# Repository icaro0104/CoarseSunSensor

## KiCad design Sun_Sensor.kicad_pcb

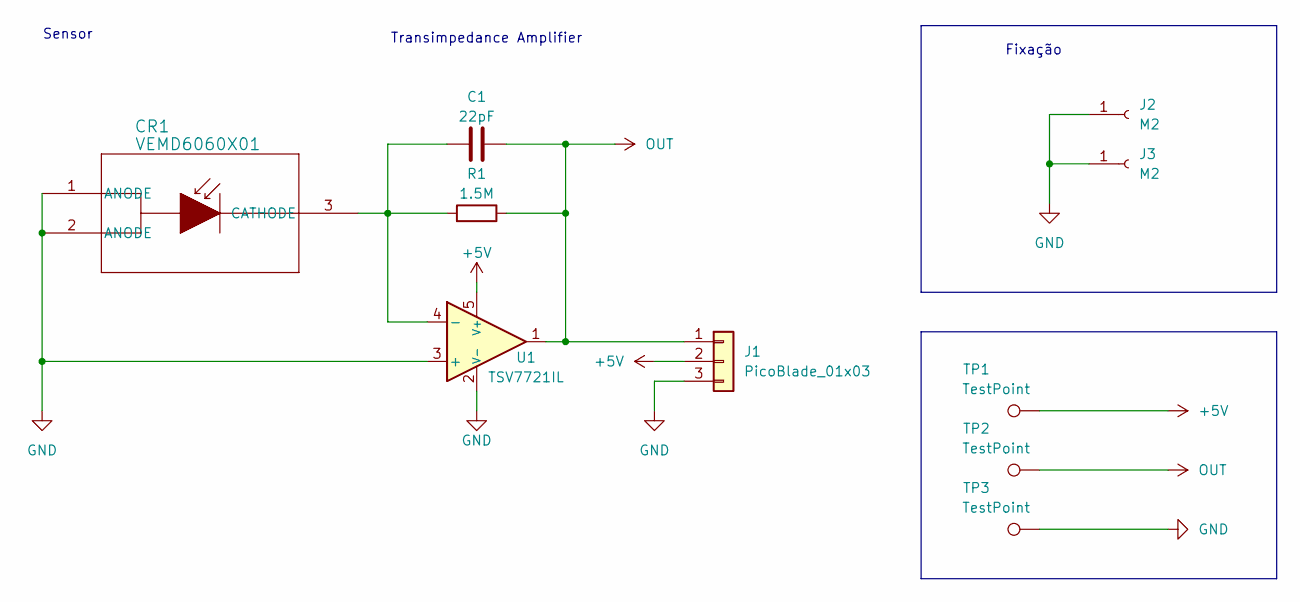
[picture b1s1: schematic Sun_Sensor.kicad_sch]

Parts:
C1: 22pF; C_0805_2012Metric_Pad1.15x1.40mm_HandSolder
CR1: VEMD6060X01
J1: PicoBlade_01x03; Molex_PicoBlade_53047-0310_1x03_P1.25mm_Vertical
J2, J3: M2; MountingHole_2.2mm_M2_DIN965_Pad_TopOnly
R1: 1.5M; R_0805_2012Metric_Pad1.20x1.40mm_HandSolder
TP1, TP2: TestPoint; TestPoint_THTPad_1.5x1.5mm_Drill0.7mm
TP3: TestPoint; TestPoint_2Pads_Pitch2.54mm_Drill0.8mm
U1: TSV7721IL; SOT-23-5

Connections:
+5V: J1.2, TP1.1, U1.5 (V+)
GND: CR1.1 (ANODE), CR1.2 (ANODE), J1.3, J2.1, J3.1, TP3.1, U1.2 (V-), U1.3 (+)
unnamed: C1.2, CR1.3 (CATHODE), R1.1, U1.4 (-)
OUT: C1.1, J1.1, R1.2, TP2.1, U1.1

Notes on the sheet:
Transimpedance Amplifier
Sensor
Fixação

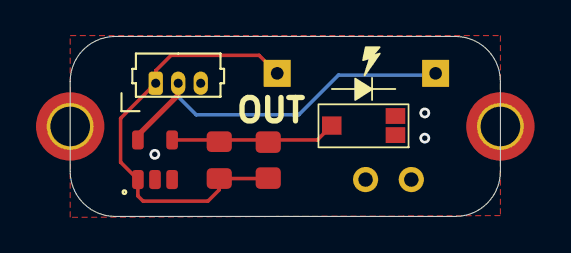
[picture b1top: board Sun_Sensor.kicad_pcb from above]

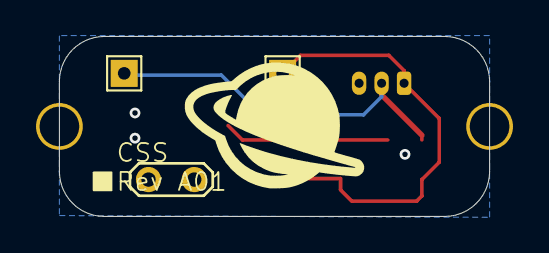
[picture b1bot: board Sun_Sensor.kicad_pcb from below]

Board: 2 copper layers, 23.9 x 10.0 mm, 10 parts (3 on the bottom side), 4 nets.

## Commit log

2024-12-11 added files
    initial commit
2024-12-16 minor reposition
    Minor reposition of test-hook
2024-12-16 minor CAN bus topology changes and label changes
    minor CAN bus topology changes and Component Label changes
